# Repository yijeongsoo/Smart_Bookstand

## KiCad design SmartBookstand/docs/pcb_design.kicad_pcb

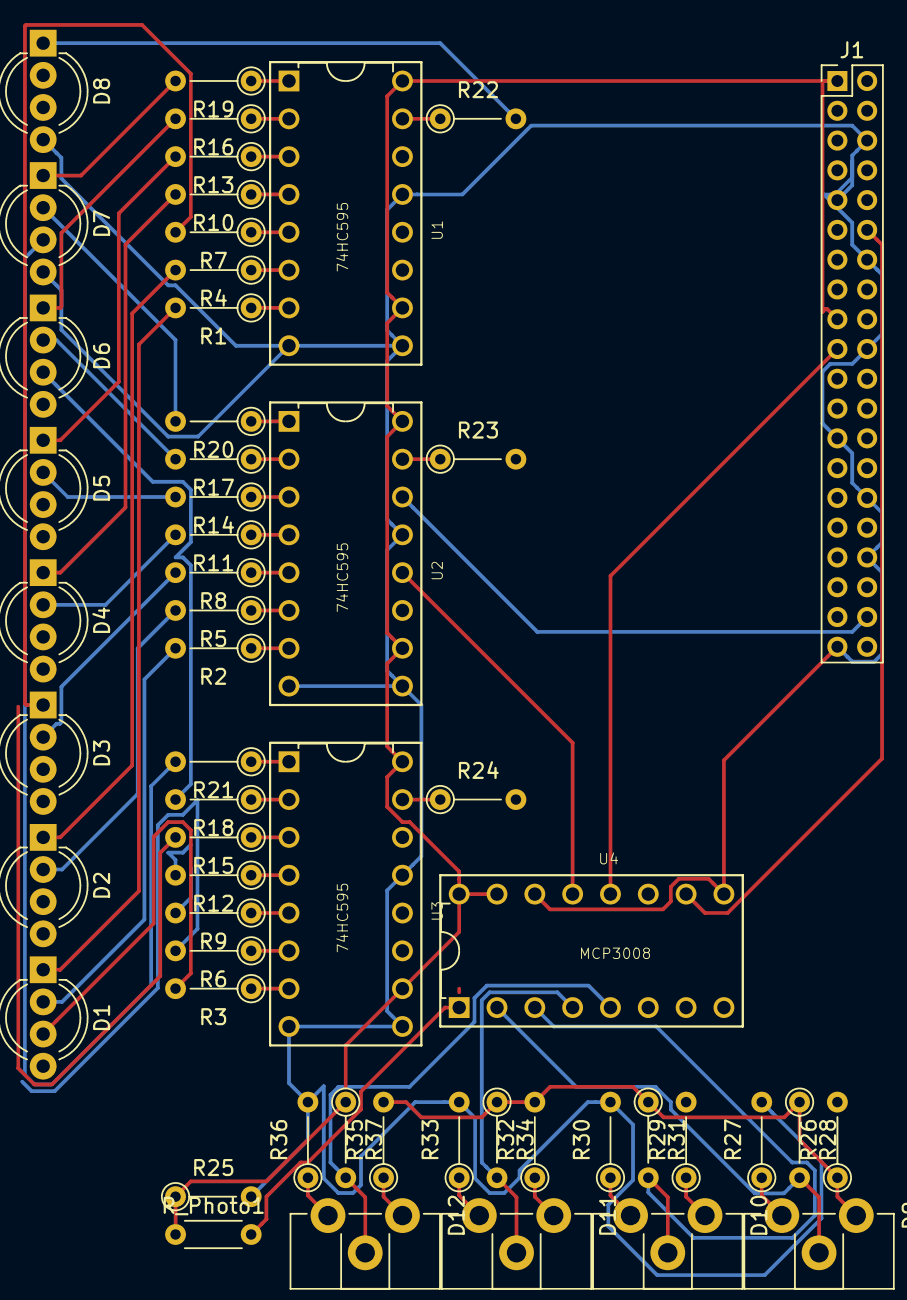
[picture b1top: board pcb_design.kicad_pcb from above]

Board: 2 copper layers, 55 parts (0 on the bottom side), 71 nets.

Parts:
D1, D2, D3, D4, D5, D6, D7, D8: LED_RGBA; LED_D5.0mm-4_RGB_Wide_Pins
D9, D10, D11, D12: LinearPotentiometer_copy; Potentiometer_ACP_CA9-H2,5_Horizontal
J1: Conn_02x20_Odd_Even; PinHeader_2x20_P2.00mm_Vertical
R1, R4, R7, R10, R13, R16, R19, R22: 470; R_Axial_DIN0204_L3.6mm_D1.6mm_P5.08mm_Vertical
R2, R3, R5, R6, R8, R9, R11, R12, R14, R15, R17, R18, R20, R21, R23, R24: 1K; R_Axial_DIN0204_L3.6mm_D1.6mm_P5.08mm_Vertical
R25, R26, R27, R29, R30, R32, R33, R35, R36: 10K; R_Axial_DIN0204_L3.6mm_D1.6mm_P5.08mm_Vertical
R28, R31, R34, R37: 100K; R_Axial_DIN0204_L3.6mm_D1.6mm_P5.08mm_Vertical
R_Photo1: ???; R_Axial_DIN0204_L3.6mm_D1.6mm_P5.08mm_Horizontal
U1, U2, U3: 74HC595; DIP16-2.54-19.2X7.62MM
U4: MCP3008; DIP16-2.54-19.2X7.62MM

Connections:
/3.3V: J1.1, J1.17, R25.1, R26.1, R28.1, R31.1, R32.2, R34.1, R35.2, R37.1, R_Photo1.1, U1.10, U1.16, U2.10, U2.16, U3.10, U3.16, U4.15, U4.16
/5V: J1.2, J1.4
/ADC_CH0: R_Photo1.2, U4.1
/ADC_CH1: D9.2, R28.2, U4.2
/ADC_CH2: D10.2, R31.2, U4.3
/ADC_CH3: D11.2, R34.2, U4.4
/ADC_CH4: D12.2, R37.2, U4.5
/GND: D1.4, D2.4, D3.4, D4.4, D5.4, D6.4, D7.4, D8.4, J1.6, J1.9, J1.14, J1.20, J1.25, J1.30, J1.34, J1.39, R25.2, R27.2, R30.2, R33.2, R36.2, U1.8, U1.9, U1.13, U2.8, U2.9, U2.13, U3.8, U3.9, U3.13, U4.9, U4.14
/GPIO10: J1.19, U4.12
/GPIO11: J1.23, U2.12, U4.13
/GPIO12: J1.32, U1.12
/GPIO18: J1.12, U4.10
/GPIO20: J1.38, U1.14, U2.14, U3.14
/GPIO21: J1.40, U1.11, U2.11, U3.11
/GPIO26: J1.37, U3.12
/U1_QA: R1.1, U1.15
/U1_QB: R4.1, U1.1
/U1_QC: R7.1, U1.2
/U1_QD: R10.1, U1.3
/U1_QE: R13.1, U1.4
/U1_QF: R16.1, U1.5
/U1_QG: R19.1, U1.6
/U1_QH: R22.1, U1.7
/U2_QA: R2.1, U2.15
/U2_QB: R5.1, U2.1
/U2_QC: R8.1, U2.2
/U2_QD: R11.1, U2.3
/U2_QE: R14.1, U2.4
/U2_QF: R17.1, U2.5
/U2_QG: R20.1, U2.6
/U2_QH: R23.1, U2.7
/U3_QA: R3.1, U3.15
/U3_QB: R6.1, U3.1
/U3_QC: R9.1, U3.2
/U3_QD: R12.1, U3.3
/U3_QE: R15.1, U3.4
/U3_QF: R18.1, U3.5
/U3_QG: R21.1, U3.6
/U3_QH: R24.1, U3.7
unnamed: D1.1, R1.2
unnamed: D1.2, R2.2
unnamed: D1.3, R3.2
unnamed: D2.1, R4.2
unnamed: D2.2, R5.2
unnamed: D2.3, R6.2
unnamed: D3.1, R7.2
unnamed: D3.2, R8.2
unnamed: D3.3, R9.2
unnamed: D4.1, R10.2
unnamed: D4.2, R11.2
unnamed: D4.3, R12.2
unnamed: D5.1, R13.2
unnamed: D5.2, R14.2
unnamed: D5.3, R15.2
unnamed: D6.1, R16.2
unnamed: D6.2, R17.2
unnamed: D6.3, R18.2
unnamed: D7.1, R19.2
unnamed: D7.2, R20.2
unnamed: D7.3, R21.2
unnamed: D8.1, R22.2
unnamed: D8.2, R23.2
unnamed: D8.3, R24.2
unnamed: D9.1, R26.2
unnamed: D9.3, R27.1
unnamed: D10.1, R29.1
unnamed: D10.3, R30.1
unnamed: D11.1, R32.1
unnamed: D11.3, R33.1
unnamed: D12.1, R35.1
unnamed: D12.3, R36.1
